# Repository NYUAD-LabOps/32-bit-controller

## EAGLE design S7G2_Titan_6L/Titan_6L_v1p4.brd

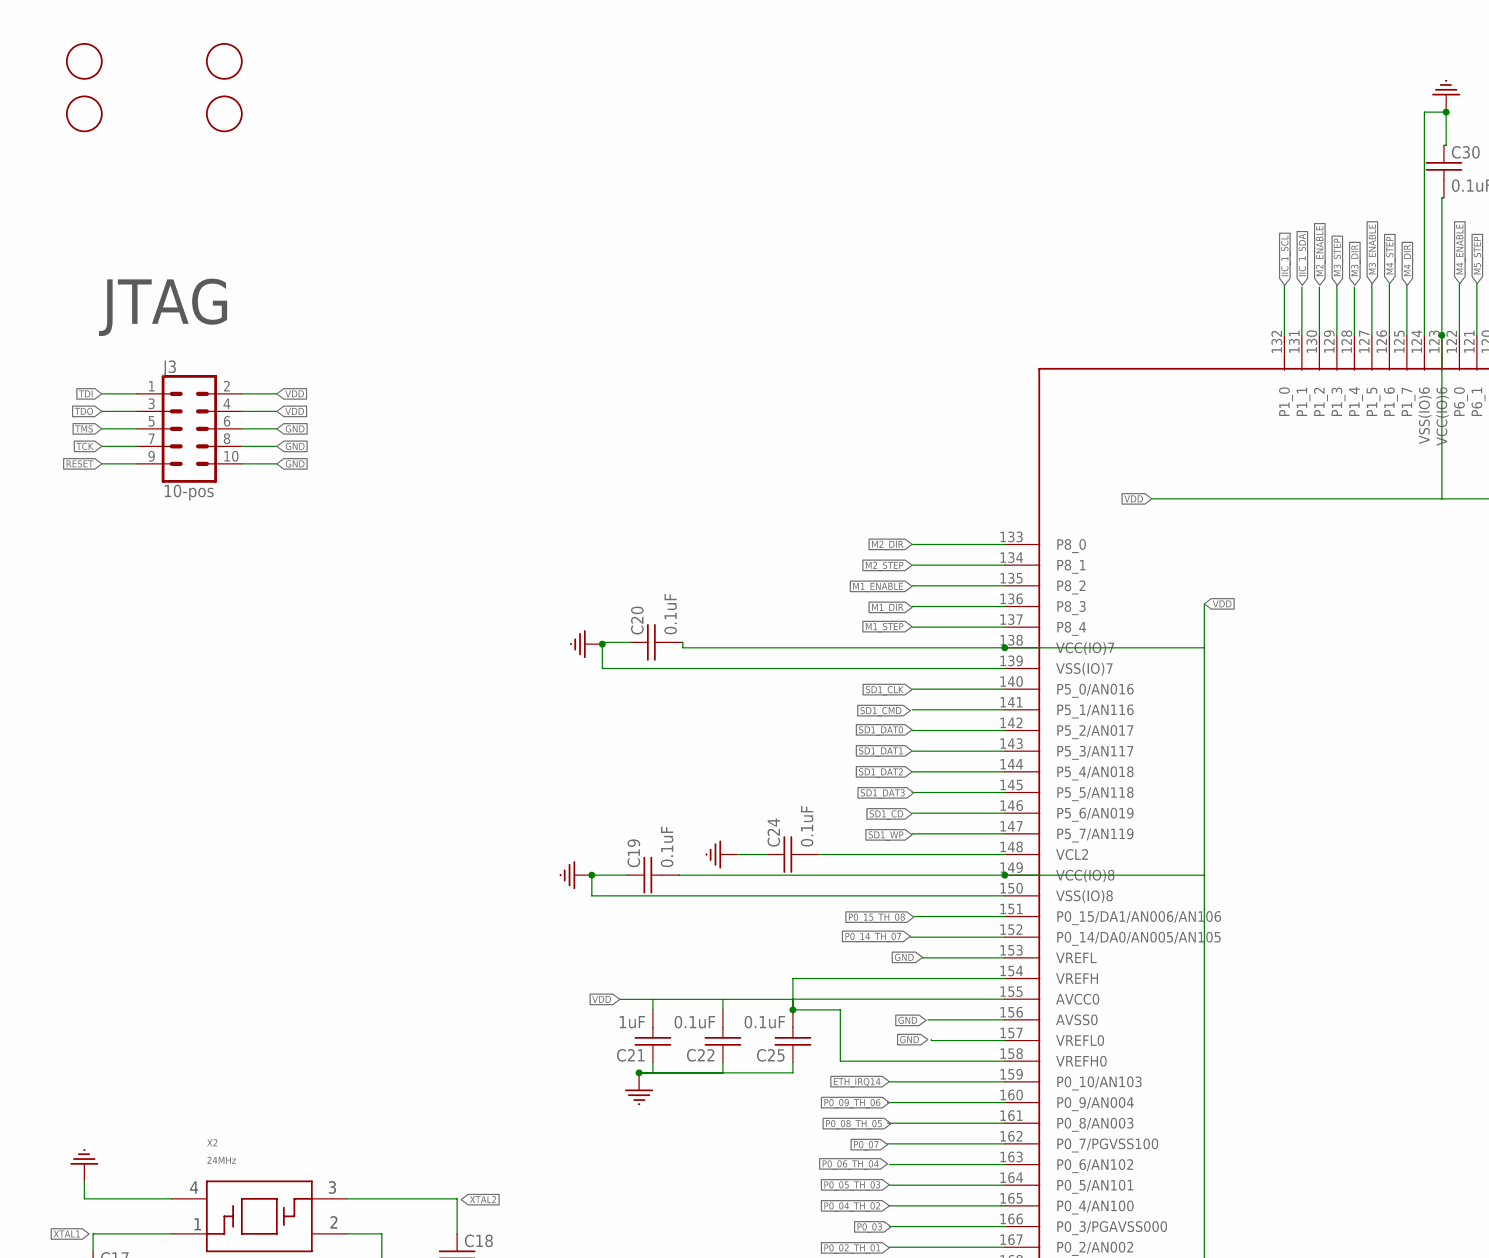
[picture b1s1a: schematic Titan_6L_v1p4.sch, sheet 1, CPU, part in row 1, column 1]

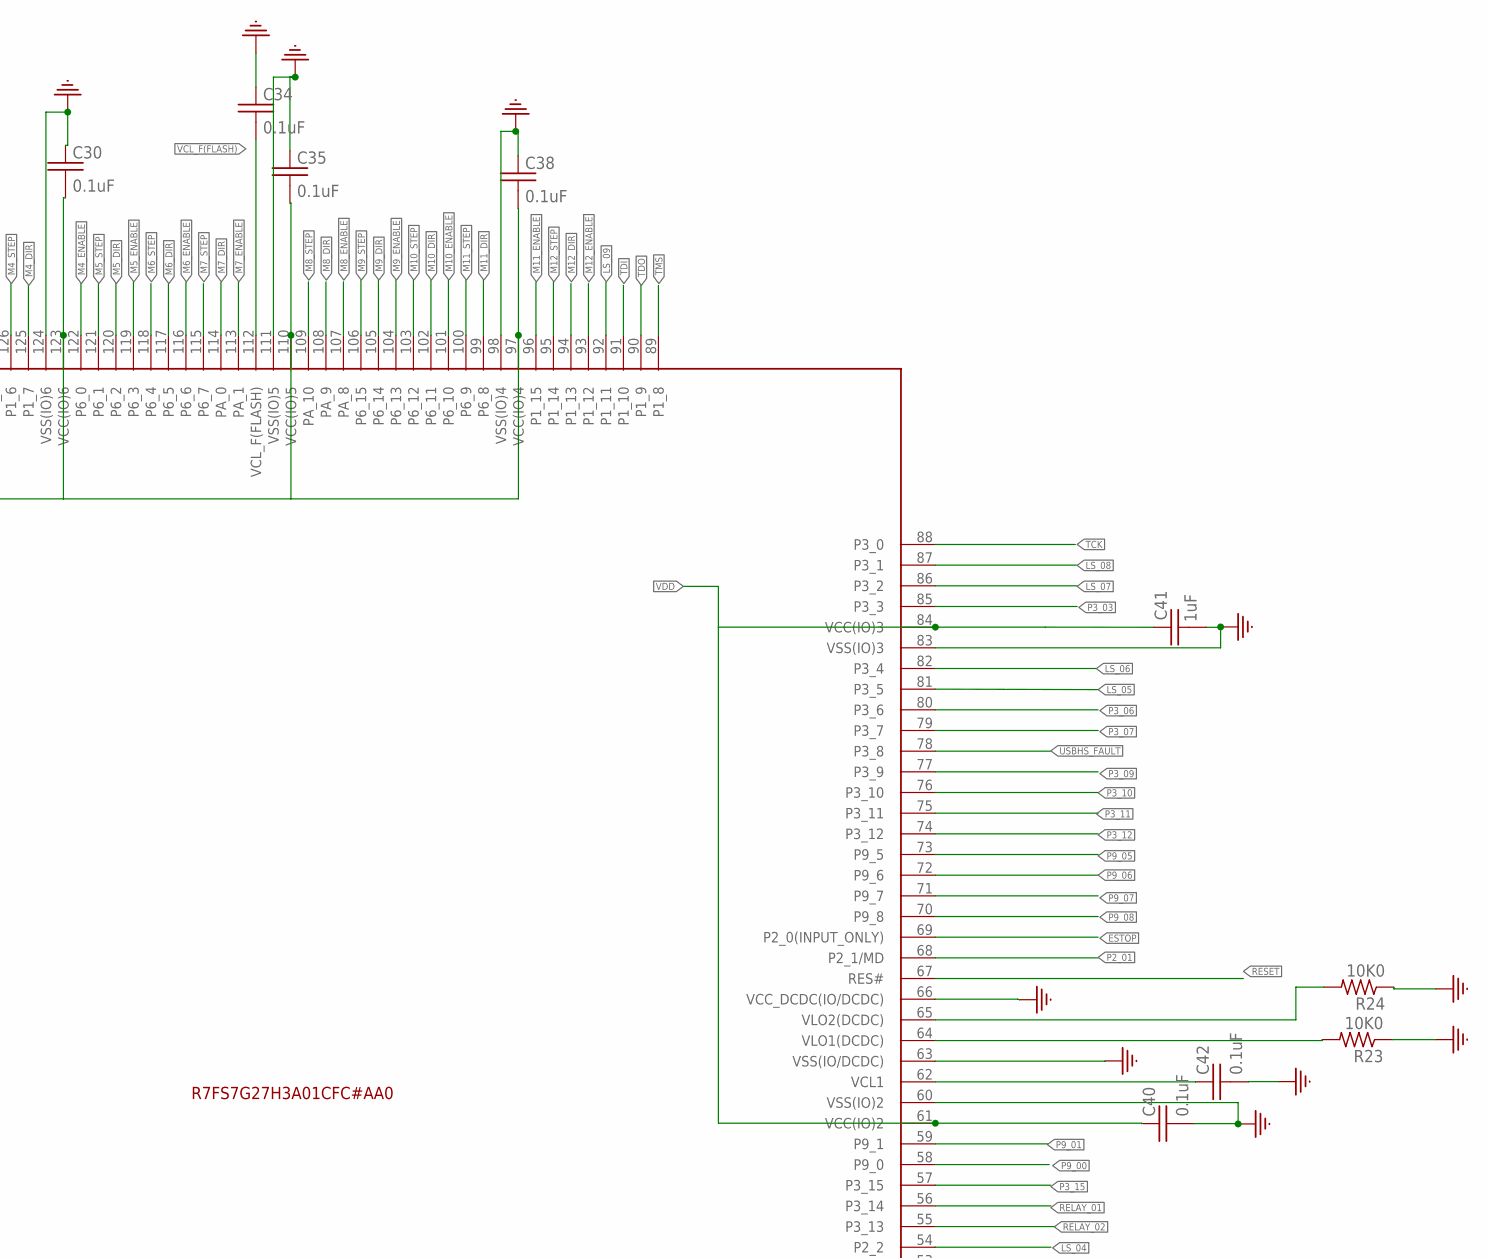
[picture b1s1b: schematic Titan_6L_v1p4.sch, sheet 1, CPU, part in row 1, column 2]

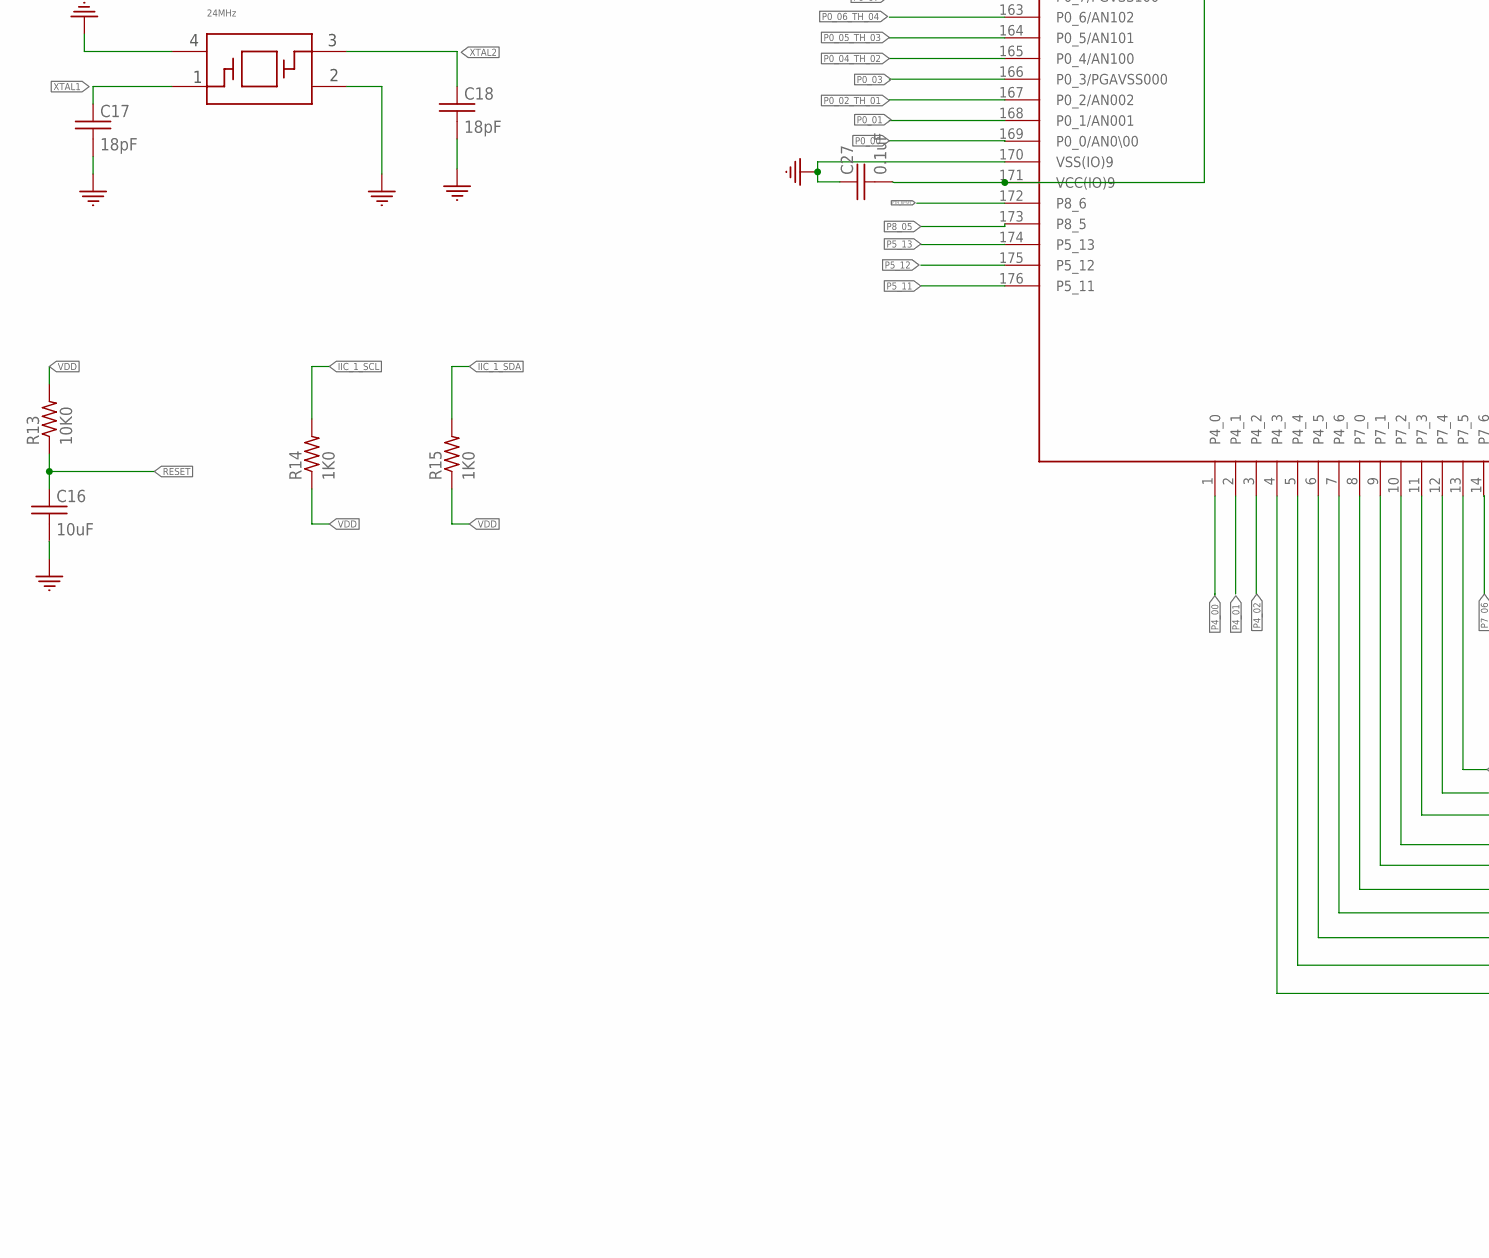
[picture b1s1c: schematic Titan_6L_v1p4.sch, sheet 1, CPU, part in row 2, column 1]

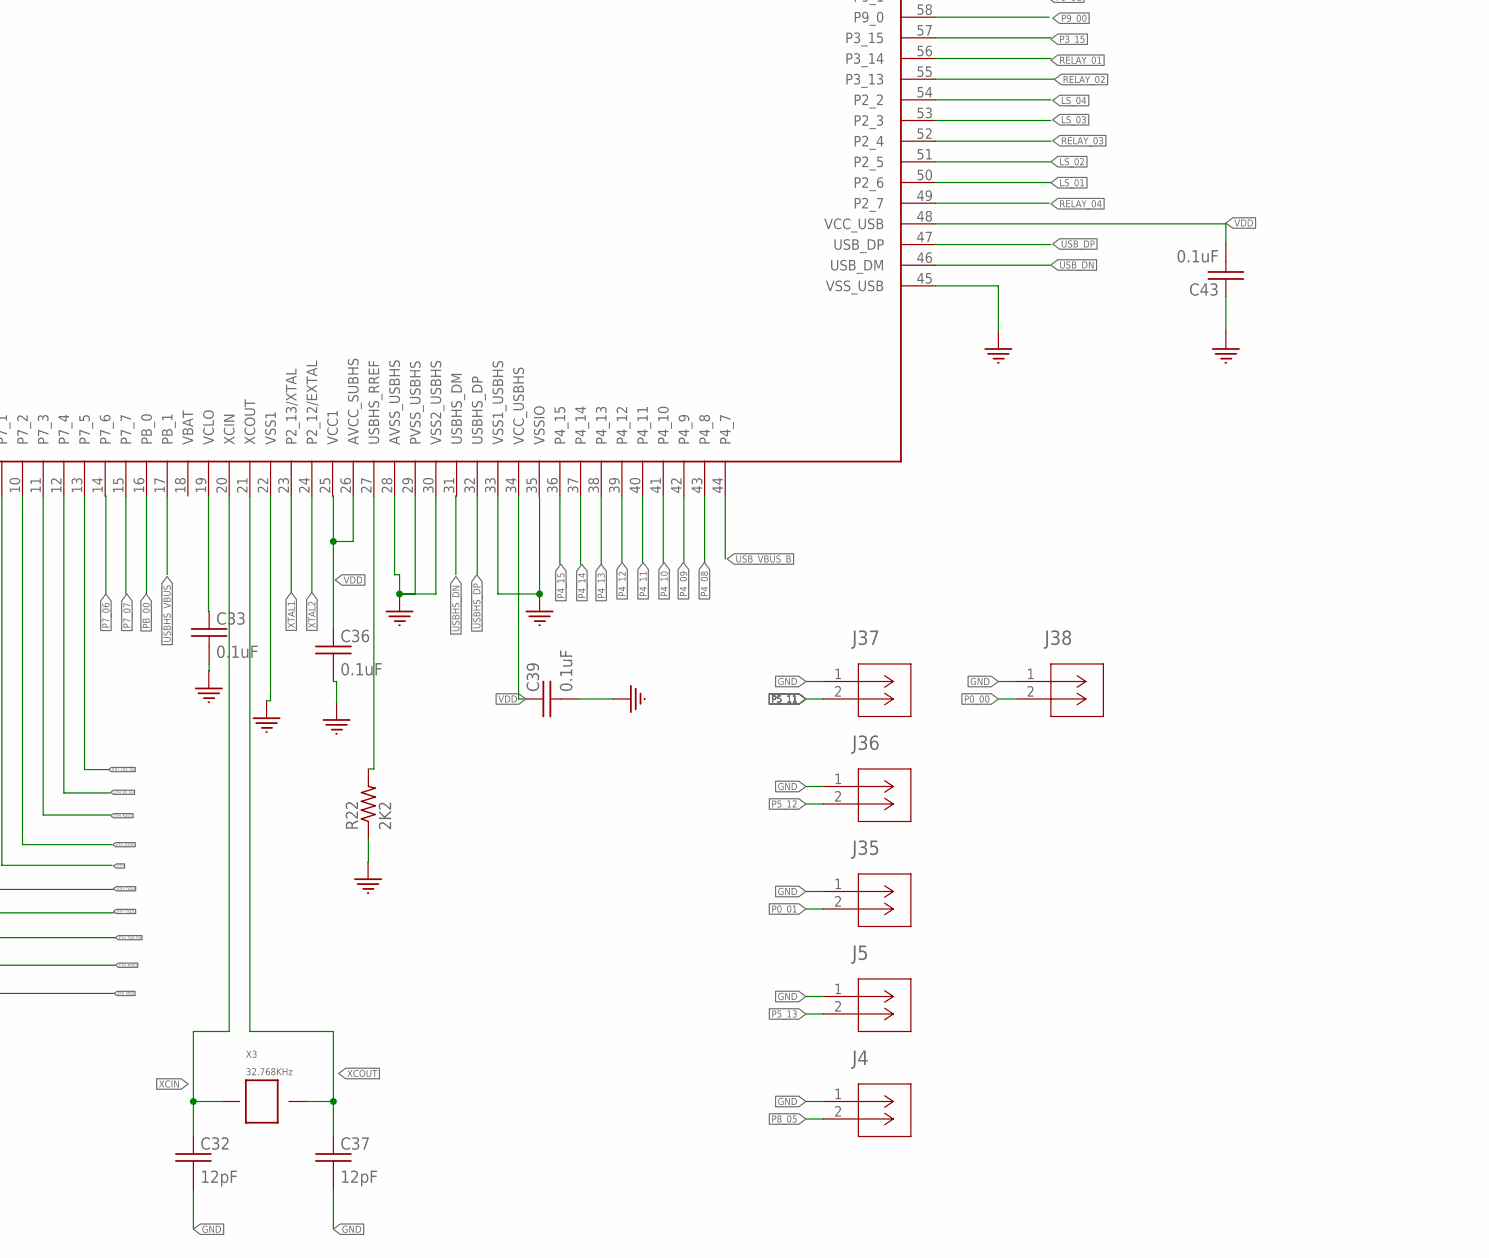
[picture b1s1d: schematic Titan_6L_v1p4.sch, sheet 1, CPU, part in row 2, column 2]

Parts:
AFID1, AFID2, AFID4, AFID5: FIDUCIAL_1MM
C16: 10uF; 0402
C17, C18: 18pF; 0402
C19, C20, C22, C24, C25, C27, C30, C33, C34, C35, C36, C38, C39, C40, C42, C43: 0.1uF; 0402
C21, C41: 1uF; 0402
C32, C37: 12pF; 0402
J3: 10-pos; 2X5
J4, J5, J35, J36, J37, J38: CONN_530470210_PICOBLADE_X_2; CON_530470210_MOL
R13, R23, R24: 10K0; 0402
R14, R15: 1K0; 0402
R22: 2K2; 0402
U3: S7G2LQFP176; LQFP176_24X24
X2: 24MHz; SMD_3225
X3: 32.768KHz; SMD_X_2_PADS

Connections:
ESTOP: U3.69 (P2_0(INPUT_ONLY)); also elsewhere on the board
ETH: U3.9 (P7_1); also elsewhere on the board
ETH_CRS_DV: U3.13 (P7_5); also elsewhere on the board
ETH_IRQ14: U3.159 (P0_10/AN103); also elsewhere on the board
ETH_MDC: U3.4 (P4_3); also elsewhere on the board
ETH_MDIO: U3.5 (P4_4); also elsewhere on the board
ETH_RESET: U3.172 (P8_6); also elsewhere on the board
ETH_RXD0: U3.10 (P7_2); also elsewhere on the board
ETH_RXD1: U3.11 (P7_3); also elsewhere on the board
ETH_RX_ER: U3.12 (P7_4); also elsewhere on the board
ETH_TXD0: U3.8 (P7_0); also elsewhere on the board
ETH_TXD1: U3.7 (P4_6); also elsewhere on the board
ETH_TXD_EN: U3.6 (P4_5); also elsewhere on the board
GND: C16.2, C17.2, C18.2, C19.1, C20.1, C21.1, C22.1, C24.1, C25.1, C27.1, C30.1, C32.2, C33.2, C34.1, C35.1, C36.2, C37.2, C38.1, C39.2, C40.2, C41.2, C42.2, C43.1, J3.6, J3.8, J3.10, J4.1, J5.1, J35.1, J36.1, J37.1, J38.1, R22.1, R23.1, R24.1, U3.22 (VSS1), U3.28 (AVSS_USBHS), U3.29 (PVSS_USBHS), U3.30 (VSS2_USBHS), U3.33 (VSS1_USBHS), U3.35 (VSSIO), U3.45 (VSS_USB), U3.60 (VSS(IO)2), U3.63 (VSS(IO/DCDC)), U3.66 (VCC_DCDC(IO/DCDC)), U3.83 (VSS(IO)3), U3.98 (VSS(IO)4), U3.111 (VSS(IO)5), U3.124 (VSS(IO)6), U3.139 (VSS(IO)7), U3.150 (VSS(IO)8), U3.153 (VREFL), U3.156 (AVSS0), U3.157 (VREFL0), U3.170 (VSS(IO)9), X2.2, X2.4; also elsewhere on the board
IIC_1_SCL: R14.2, U3.132 (P1_0)
IIC_1_SDA: R15.2, U3.131 (P1_1)
LS_01: U3.50 (P2_6); also elsewhere on the board
LS_02: U3.51 (P2_5); also elsewhere on the board
LS_03: U3.53 (P2_3); also elsewhere on the board
LS_04: U3.54 (P2_2); also elsewhere on the board
LS_05: U3.81 (P3_5); also elsewhere on the board
LS_06: U3.82 (P3_4); also elsewhere on the board
LS_07: U3.86 (P3_2); also elsewhere on the board
LS_08: U3.87 (P3_1); also elsewhere on the board
LS_09: U3.92 (P1_11); also elsewhere on the board
M1_DIR: U3.136 (P8_3); also elsewhere on the board
M1_ENABLE: U3.135 (P8_2); also elsewhere on the board
M1_STEP: U3.137 (P8_4); also elsewhere on the board
M2_DIR: U3.133 (P8_0); also elsewhere on the board
M2_ENABLE: U3.130 (P1_2); also elsewhere on the board
M2_STEP: U3.134 (P8_1); also elsewhere on the board
M3_DIR: U3.128 (P1_4); also elsewhere on the board
M3_ENABLE: U3.127 (P1_5); also elsewhere on the board
M3_STEP: U3.129 (P1_3); also elsewhere on the board
M4_DIR: U3.125 (P1_7); also elsewhere on the board
M4_ENABLE: U3.122 (P6_0); also elsewhere on the board
M4_STEP: U3.126 (P1_6); also elsewhere on the board
M5_DIR: U3.120 (P6_2); also elsewhere on the board
M5_ENABLE: U3.119 (P6_3); also elsewhere on the board
M5_STEP: U3.121 (P6_1); also elsewhere on the board
M6_DIR: U3.117 (P6_5); also elsewhere on the board
M6_ENABLE: U3.116 (P6_6); also elsewhere on the board
M6_STEP: U3.118 (P6_4); also elsewhere on the board
M7_DIR: U3.114 (PA_0); also elsewhere on the board
M7_ENABLE: U3.113 (PA_1); also elsewhere on the board
M7_STEP: U3.115 (P6_7); also elsewhere on the board
M8_DIR: U3.108 (PA_9); also elsewhere on the board
M8_ENABLE: U3.107 (PA_8); also elsewhere on the board
M8_STEP: U3.109 (PA_10); also elsewhere on the board
M9_DIR: U3.105 (P6_14); also elsewhere on the board
M9_ENABLE: U3.104 (P6_13); also elsewhere on the board
M9_STEP: U3.106 (P6_15); also elsewhere on the board
M10_DIR: U3.102 (P6_11); also elsewhere on the board
M10_ENABLE: U3.101 (P6_10); also elsewhere on the board
M10_STEP: U3.103 (P6_12); also elsewhere on the board
M11_DIR: U3.99 (P6_8); also elsewhere on the board
M11_ENABLE: U3.96 (P1_15); also elsewhere on the board
M11_STEP: U3.100 (P6_9); also elsewhere on the board
M12_DIR: U3.94 (P1_13); also elsewhere on the board
M12_ENABLE: U3.93 (P1_12); also elsewhere on the board
M12_STEP: U3.95 (P1_14); also elsewhere on the board
unnamed: C24.2, U3.148 (VCL2)
unnamed: C33.1, U3.19 (VCLO)
unnamed: C42.1, U3.62 (VCL1)
unnamed: R23.2, U3.64 (VLO1(DCDC))
unnamed: R24.2, U3.65 (VLO2(DCDC))
unnamed: R22.2, U3.27 (USBHS_RREF)
P0_00: J38.2, U3.169 (P0_0/AN0\00)
P0_01: J35.2, U3.168 (P0_1/AN001)
P0_02_TH_01: U3.167 (P0_2/AN002); also elsewhere on the board
P0_03: U3.166 (P0_3/PGAVSS000)
P0_04_TH_02: U3.165 (P0_4/AN100); also elsewhere on the board
P0_05_TH_03: U3.164 (P0_5/AN101); also elsewhere on the board
P0_06_TH_04: U3.163 (P0_6/AN102); also elsewhere on the board
P0_07: U3.162 (P0_7/PGVSS100)
P0_08_TH_05: U3.161 (P0_8/AN003); also elsewhere on the board
P0_09_TH_06: U3.160 (P0_9/AN004); also elsewhere on the board
P0_14_TH_07: U3.152 (P0_14/DA0/AN005/AN105); also elsewhere on the board
P0_15_TH_08: U3.151 (P0_15/DA1/AN006/AN106); also elsewhere on the board
P2_01: U3.68 (P2_1/MD)
P3_03: U3.85 (P3_3)
P3_06: U3.80 (P3_6)
P3_07: U3.79 (P3_7)
P3_09: U3.77 (P3_9)
P3_10: U3.76 (P3_10); also elsewhere on the board
P3_11: U3.75 (P3_11); also elsewhere on the board
P3_12: U3.74 (P3_12); also elsewhere on the board
P3_15: U3.57 (P3_15); also elsewhere on the board
P4_00: U3.1 (P4_0)
P4_01: U3.2 (P4_1)
P4_02: U3.3 (P4_2)
P4_08: U3.43 (P4_8)
P4_09: U3.42 (P4_9)
P4_10: U3.41 (P4_10)
P4_11: U3.40 (P4_11)
P4_12: U3.39 (P4_12)
P4_13: U3.38 (P4_13)
P4_14: U3.37 (P4_14)
P4_15: U3.36 (P4_15)
P5_11: J37.2, U3.176 (P5_11)
P5_12: J36.2, U3.175 (P5_12)
P5_13: J5.2, U3.174 (P5_13)
P7_06: U3.14 (P7_6)
P7_07: U3.15 (P7_7)
P8_05: J4.2, U3.173 (P8_5)
P9_00: U3.58 (P9_0); also elsewhere on the board
P9_01: U3.59 (P9_1); also elsewhere on the board
P9_05: U3.73 (P9_5); also elsewhere on the board
P9_06: U3.72 (P9_6); also elsewhere on the board
P9_07: U3.71 (P9_7); also elsewhere on the board
P9_08: U3.70 (P9_8); also elsewhere on the board
PB_00: U3.16 (PB_0)
RELAY_01: U3.56 (P3_14); also elsewhere on the board
RELAY_02: U3.55 (P3_13); also elsewhere on the board
RELAY_03: U3.52 (P2_4); also elsewhere on the board
RELAY_04: U3.49 (P2_7); also elsewhere on the board
RESET: C16.1, J3.9, R13.1, U3.67 (RES#)
SD1_CD: U3.146 (P5_6/AN019); also elsewhere on the board
SD1_CLK: U3.140 (P5_0/AN016); also elsewhere on the board
SD1_CMD: U3.141 (P5_1/AN116); also elsewhere on the board
SD1_DAT0: U3.142 (P5_2/AN017); also elsewhere on the board
SD1_DAT1: U3.143 (P5_3/AN117); also elsewhere on the board
SD1_DAT2: U3.144 (P5_4/AN018); also elsewhere on the board
SD1_DAT3: U3.145 (P5_5/AN118); also elsewhere on the board
SD1_WP: U3.147 (P5_7/AN119); also elsewhere on the board
TCK: J3.7, U3.88 (P3_0)
TDI: J3.1, U3.91 (P1_10)
TDO: J3.3, U3.90 (P1_9)
TMS: J3.5, U3.89 (P1_8)
USBHS_DN: U3.31 (USBHS_DM); also elsewhere on the board
USBHS_DP: U3.32 (USBHS_DP); also elsewhere on the board
USBHS_FAULT: U3.78 (P3_8); also elsewhere on the board
USBHS_VBUS: U3.17 (PB_1); also elsewhere on the board
USB_DN: U3.46 (USB_DM); also elsewhere on the board
USB_DP: U3.47 (USB_DP); also elsewhere on the board
USB_VBUS_B: U3.44 (P4_7); also elsewhere on the board
VCL_F(FLASH): C34.2, U3.112 (VCL_F(FLASH))
VDD: C19.2, C20.2, C21.2, C22.2, C25.2, C27.2, C30.2, C35.2, C36.1, C38.2, C39.1, C40.1, C41.1, C43.2, J3.2, J3.4, R13.2, R14.1, R15.1, U3.25 (VCC1), U3.26 (AVCC_SUBHS), U3.34 (VCC_USBHS), U3.48 (VCC_USB), U3.61 (VCC(IO)2), U3.84 (VCC(IO)3), U3.97 (VCC(IO)4), U3.110 (VCC(IO)5), U3.123 (VCC(IO)6), U3.138 (VCC(IO)7), U3.149 (VCC(IO)8), U3.154 (VREFH), U3.155 (AVCC0), U3.158 (VREFH0), U3.171 (VCC(IO)9); also elsewhere on the board
XCIN: C32.1, U3.20 (XCIN), X3.P$1
XCOUT: C37.1, U3.21 (XCOUT), X3.P$2
XTAL1: C17.1, U3.23 (P2_13/XTAL), X2.1
XTAL2: C18.1, U3.24 (P2_12/EXTAL), X2.3

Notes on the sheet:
JTAG

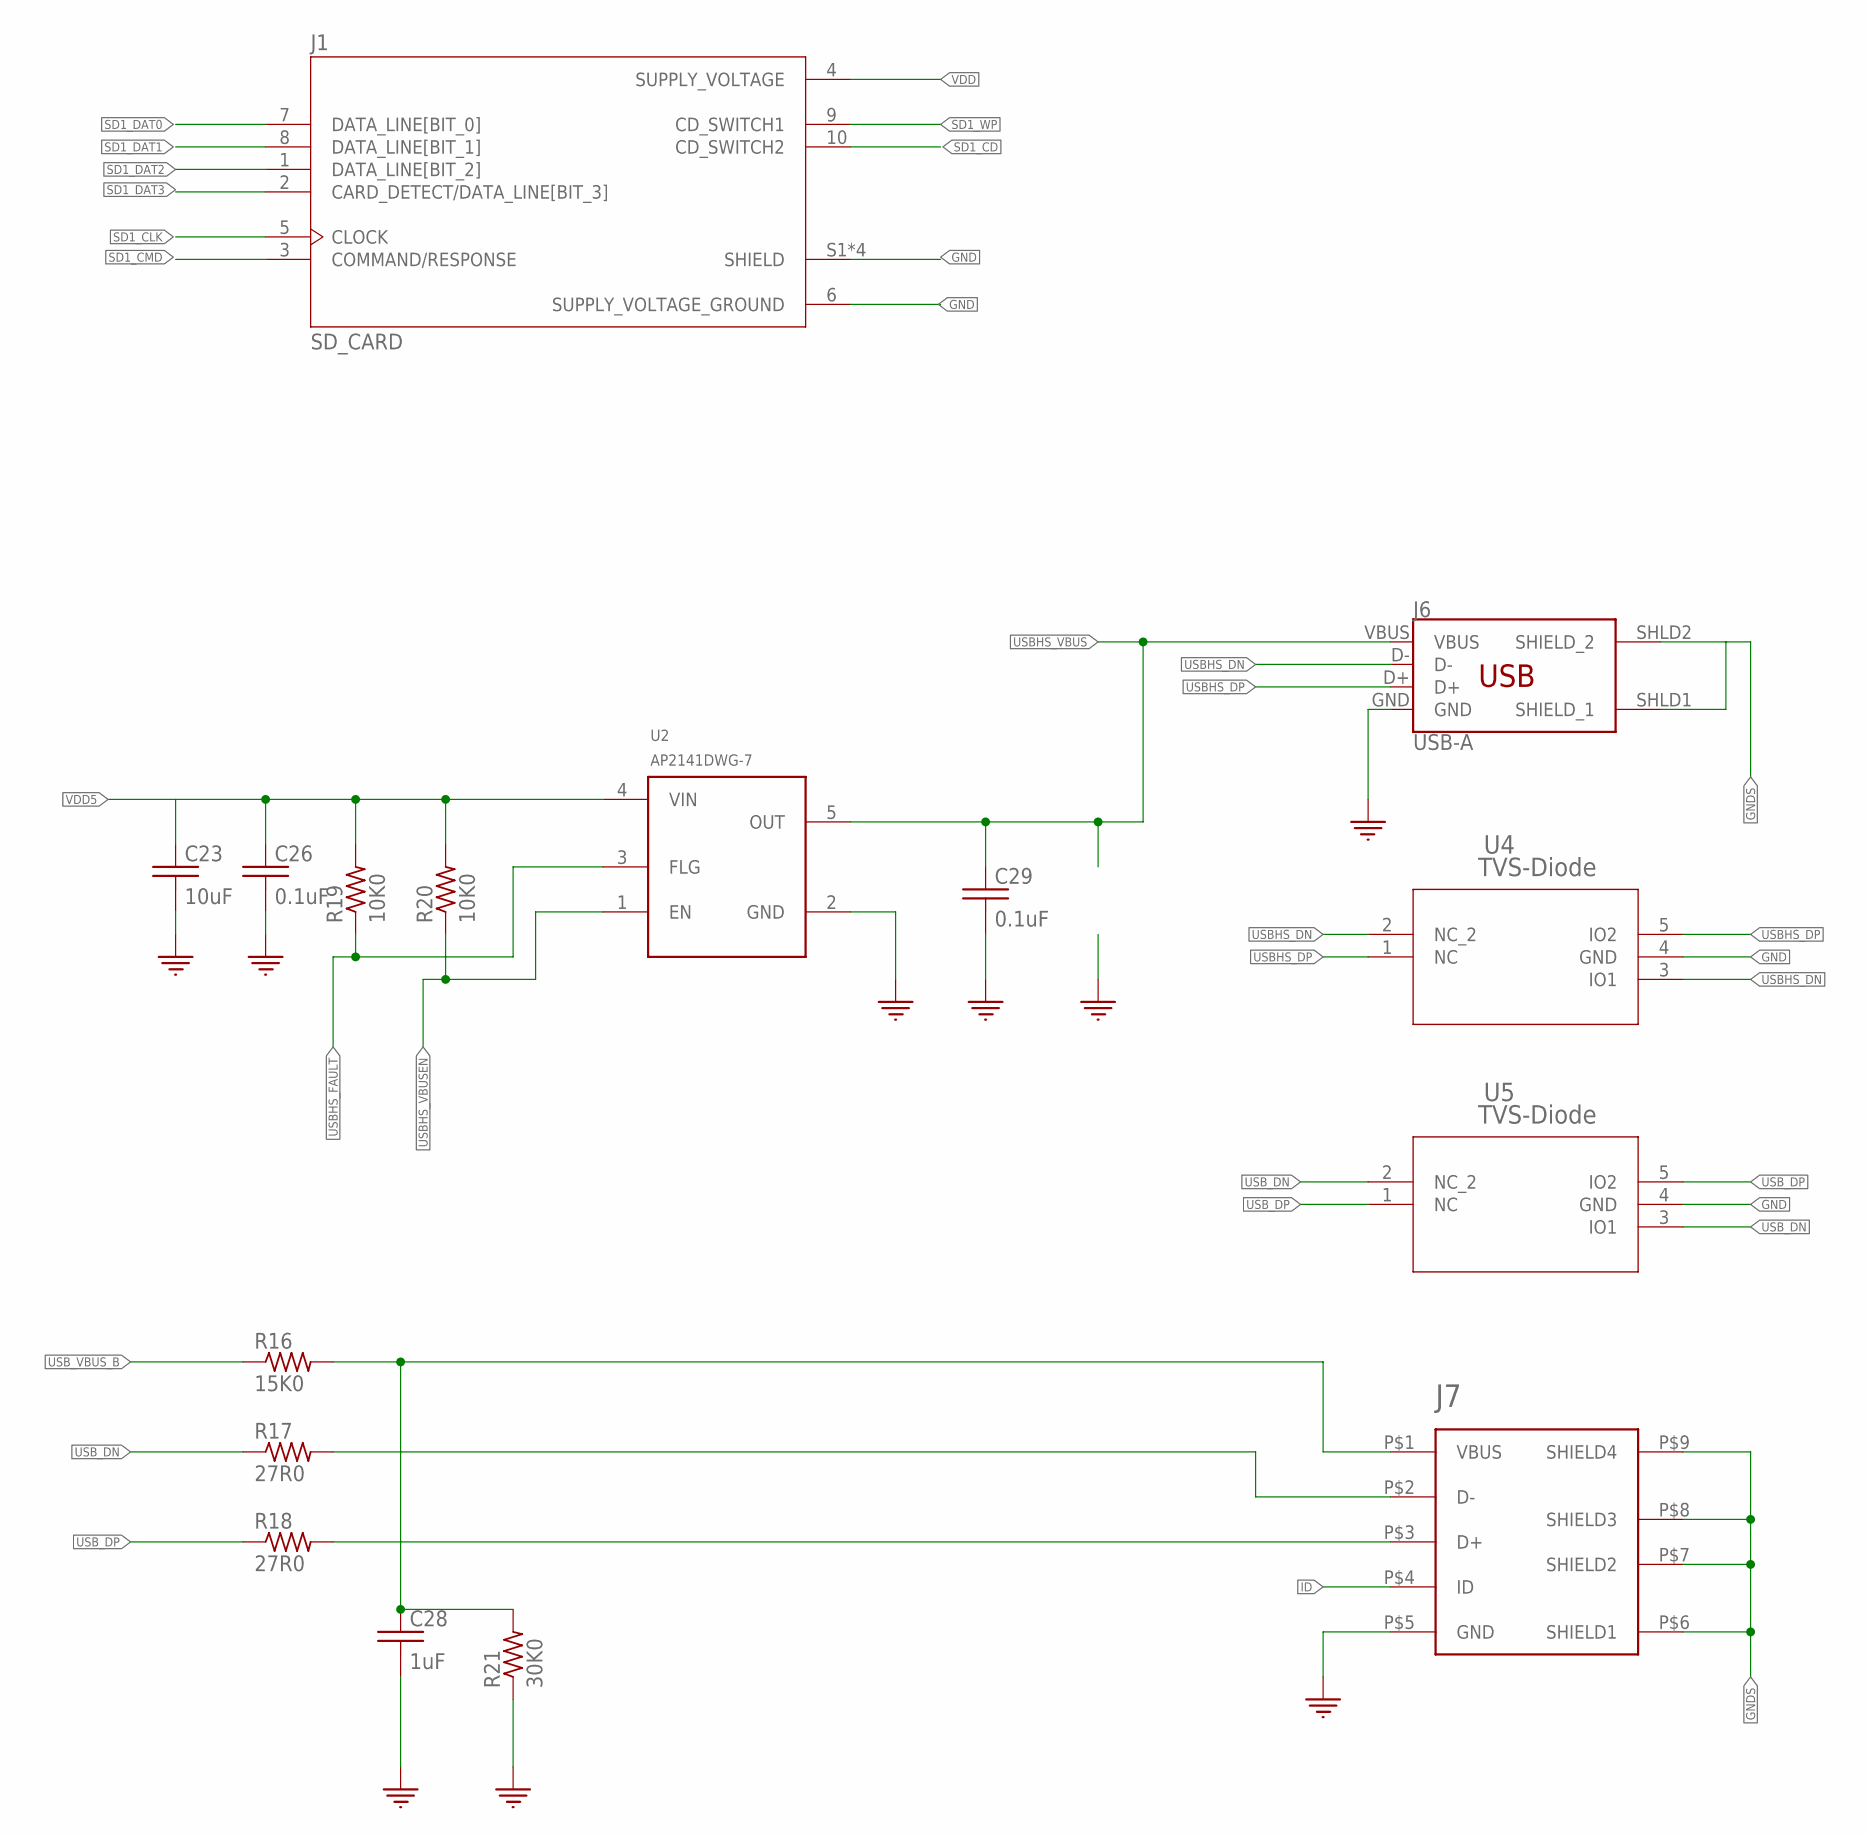
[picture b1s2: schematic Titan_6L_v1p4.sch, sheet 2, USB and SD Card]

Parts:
C23: 10uF; 0402
C26, C29: 0.1uF; 0402
C28: 1uF; 0402
J1: SD_CARD
J6: USB-A; USB_A_SMT
J7: USB-B-Micro; USB_MICRO-B
R16: 15K0; 0402
R17, R18: 27R0; 0402
R19, R20: 10K0; 0402
R21: 30K0; 0402
U2: AP2151DWG-7; SOT-23-5
U4, U5: TVS-Diode; DRL5

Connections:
D+: J7.P$3 (D+), R18.2
D-: J7.P$2 (D-), R17.2
GND: C23.2, C26.2, C28.2, C29.2, J1.6 (SUPPLY_VOLTAGE_GROUND), J1.S1 (SHIELD), J1.S2 (SHIELD), J1.S3 (SHIELD), J1.S4 (SHIELD), J6.GND, J7.P$5 (GND), R21.1, U2.2 (GND), U4.4 (GND), U5.4 (GND); also elsewhere on the board
GNDS: J6.SHLD1 (SHIELD_1), J6.SHLD2 (SHIELD_2), J7.P$6 (SHIELD1), J7.P$7 (SHIELD2), J7.P$8 (SHIELD3), J7.P$9 (SHIELD4); also elsewhere on the board
ID: J7.P$4 (ID)
SD1_CD: J1.10 (CD_SWITCH2); also elsewhere on the board
SD1_CLK: J1.5 (CLOCK); also elsewhere on the board
SD1_CMD: J1.3 (COMMAND/RESPONSE); also elsewhere on the board
SD1_DAT0: J1.7 (DATA_LINE[BIT_0]); also elsewhere on the board
SD1_DAT1: J1.8 (DATA_LINE[BIT_1]); also elsewhere on the board
SD1_DAT2: J1.1 (DATA_LINE[BIT_2]); also elsewhere on the board
SD1_DAT3: J1.2 (CARD_DETECT/DATA_LINE[BIT_3]); also elsewhere on the board
SD1_WP: J1.9 (CD_SWITCH1); also elsewhere on the board
USBHS_DN: J6.D-, U4.2 (NC_2), U4.3 (IO1); also elsewhere on the board
USBHS_DP: J6.D+, U4.1 (NC), U4.5 (IO2); also elsewhere on the board
USBHS_FAULT: R19.1, U2.3 (FLG); also elsewhere on the board
USBHS_VBUS: C29.1, J6.VBUS, U2.5 (OUT); also elsewhere on the board
USBHS_VBUSEN: R20.1, U2.1 (EN)
USB_DN: R17.1, U5.2 (NC_2), U5.3 (IO1); also elsewhere on the board
USB_DP: R18.1, U5.1 (NC), U5.5 (IO2); also elsewhere on the board
USB_VBUS_B: R16.1; also elsewhere on the board
VBUS: C28.1, J7.P$1 (VBUS), R16.2, R21.2
VDD: J1.4 (SUPPLY_VOLTAGE); also elsewhere on the board
VDD5: C23.1, C26.1, R19.2, R20.2, U2.4 (VIN); also elsewhere on the board

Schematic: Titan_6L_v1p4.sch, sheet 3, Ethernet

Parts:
C13, C14, C46, C51: 0.1uF; 0402
C15, C44: 24pF; 0402
C45, C50: 22uF; 0603
C47: 2.2uF; 0402
C48: .1uF; 0402
C49: 100pF; 0402
FB2/2: 120Ohm; 0805
R25, R26: 470; 0402
R74: 6k49; 0402
R75, R87: 10K; 0402
R94, R100: 1K50; 0402
R101, R107, R108, R109: 33; 0402
U6: KSZ8081_QFN_24; QFN-24-M
U$2: RJ45_WITH_ELEC; RJ45_TH_ELEC
U$3: 25MHz; SMD_3225
U$4: 10uF; 0402

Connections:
C58: C13.1, U$2.4 (CT1)
C60: C14.1, U$2.5 (CT2)
CRS_DV: R109.2, U6.15 (CRS_DV/PHYAD[1:0])
ETH: U6.16 (REF_CLK); also elsewhere on the board
ETH_CRS_DV: R109.1; also elsewhere on the board
ETH_IRQ14: R75.1, U6.18 (INTRP); also elsewhere on the board
ETH_MDC: R94.1, U6.11 (MDC); also elsewhere on the board
ETH_MDIO: R100.1, U6.10 (MDIO); also elsewhere on the board
ETH_RESET: R87.1, U6.24 (!RST), U$4.1; also elsewhere on the board
ETH_RXD0: R107.1; also elsewhere on the board
ETH_RXD1: R101.1; also elsewhere on the board
ETH_RX_ER: R108.1; also elsewhere on the board
ETH_TXD0: U6.20 (TXD0); also elsewhere on the board
ETH_TXD1: U6.21 (TXD1); also elsewhere on the board
ETH_TXD_EN: U6.19 (TXEN); also elsewhere on the board
GND: C13.2, C14.2, C15.2, C44.2, C45.2, C46.2, C47.2, C48.2, C49.2, C50.2, C51.2, R74.1, U6.22 (GND), U6.25, U$2.8, U$2.10 (GLO), U$3.2, U$3.4, U$4.2; also elsewhere on the board
GNDS: U$2.13 (GNDE0), U$2.14 (GNDE1); also elsewhere on the board
LED1/SPEED: U6.23 (LED0/ANEN_SPEED), U$2.11 (YLO)
NC: U$2.7
R51: R25.1, U$2.12 (YHI)
R52: R26.1, U$2.9 (GHI)
REXT: C49.1, R74.2, U6.9 (REXT)
RXD0: R107.2, U6.13 (RXD0)
RXD1: R101.2, U6.12 (RXD1)
RXER: R108.2, U6.17 (RXER)
RXM: U6.3 (RXM), U$2.6 (RD-)
RXP: U6.4 (RXP), U$2.3 (RD+)
TXM: U6.5 (TXM), U$2.2 (TD-)
TXP: U6.6 (TXP), U$2.1 (TD+)
VDD: C50.1, C51.1, FB2/2.1, R25.2, R26.2, R75.2, R87.2, R94.2, R100.2, U6.14 (VDDIO); also elsewhere on the board
VDD_1.2: C47.1, C48.1, U6.1 (VDD_1.2)
VDD_ENET1: C45.1, C46.1, FB2/2.2, U6.2 (VDDA_3.3)
XII: C44.1, U6.8 (XI), U$3.1
XOO: C15.1, U6.7 (XO), U$3.3

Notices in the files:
parts and their libraries:
COPYRIGHT: Copyright (C) 2022 Ultra Librarian. All rights reserved.
